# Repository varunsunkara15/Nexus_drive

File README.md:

# Nexus Drive

**Nexus Drive** is an open-hardware motor driver we are designing for a humanoid robot's joints.

The goal is a compact board that can sit near each joint actuator and drive its motor accurately and efficiently. It should also report back to the robot's main controller.

> **Status:** 🚧 Early development. Schematic in progress (power stage, gate driver, MCU, CAN-FD, encoders and sensing drawn; ERC has 0 errors; logic supplies, DC-link and input protection still to add); PCB layout not started.

---

## Repository layout

```
Nexus_drive/
├── hardware/                     KiCad 10 project (open nexus_drive.kicad_pro)
│   ├── nexus_drive.kicad_pro     Project file
│   ├── nexus_drive.kicad_sch     Root schematic sheet
│   ├── gate_driver.kicad_sch     DRV8353S gate driver and support parts
│   ├── h_bridge.kicad_sch        One half-bridge (MOSFETs, shunt, phase output), used 3× for phases A/B/C
│   ├── current_sense.kicad_sch   RC filters on the current-sense amplifier outputs
│   ├── stm32g474.kicad_sch       STM32G474METx MCU, wired to the pin plan
│   ├── can_fd.kicad_sch          TCAN1042GV CAN-FD transceiver and bus connectors
│   ├── encoders.kicad_sch        On-board MA702GQ encoder and external SPI encoder connectors
│   ├── sensing.kicad_sch         Bus and phase voltage dividers, FET and motor temperature inputs
│   ├── nexus_drive.kicad_sym     Project symbols (TCAN1042GV, MA702GQ, EMI filter)
│   ├── nexus_drive.kicad_pcb     PCB layout (not started)
│   ├── fp-lib-table, sym-lib-table   Project library tables
│   └── lib/                      Project-local symbol and footprint libraries (moteus)
├── firmware/
│   └── Comms Component Selection.ioc   STM32CubeMX pin assignment for the MCU
├── docs/
│   └── power-stage.md            Power stage design notes
├── LICENSES/, NOTICE.md          Attribution for files derived from mjbots moteus (Apache-2.0)
└── README.md
```

Folders for fabrication outputs (Gerbers, BOM, pick-and-place) and datasheets will be added as the design matures.

## Design goals

These are the intended targets. Values still marked **TBD** will be filled in as we choose parts. The power stage is described in detail in [docs/power-stage.md](docs/power-stage.md).

- **Motor type:** Brushless DC / PMSM motors used in humanoid joint actuators
- **Control:** Field-oriented control (FOC) for smooth, quiet torque control
- **Feedback:** Rotor position sensing (e.g. a magnetic encoder) and phase current sensing
- **Communication:** A bus to the robot's main controller, such as CAN / CAN-FD
- **Protection:** Over-current, over-voltage, under-voltage and over-temperature protection
- **Form factor:** Small enough to mount on or inside the joint actuator

### Planned specifications

| Parameter | Target |
| --- | --- |
| Battery | 12S3P Li-ion / LiPo: 36–50.4 V (44–48 V nominal) |
| Continuous / peak phase current | TBD (depends on the motor) |
| Microcontroller | STM32G474METx (LQFP-80, 170 MHz Cortex-M4) |
| Gate driver | TI DRV8353S (SPI-configured, integrated current-sense amplifiers) |
| MOSFETs | 6 × onsemi FDMT80080DC (80 V, 1.35 mΩ) |
| Current sensing | 3 low-side shunts (value TBD) |
| Overvoltage protection | Input TVS, bulk capacitor, 100 V ceramic DC-link bank, anti-spark connector |
| Encoder interface | 3 × SPI: on-board MA702GQ magnetic encoder, 2 external connectors |
| Communication | CAN-FD (TCAN1042GV), two daisy-chain connectors |
| Board dimensions | TBD |

### Note: bulk capacitance on the battery bus

The power stage in this repo has **no bulk / DC-link capacitor bank yet**. It is owned by another team member and must be added before the board is built. The reference design (moteus x1) uses 36 × 4.7 µF 100 V ceramics. A **bulk electrolytic (or tantalum) capacitor** at the power input may also be needed. Reasons:

- **Hot-plug ringing:** a bank of only ceramics has very low ESR. Together with the battery cable's inductance, it can ring up to ~2× the battery voltage when the battery is plugged in (~100 V on a 50.4 V pack), above the 80 V MOSFET rating. An electrolytic's higher ESR (≈ 0.05–0.1 Ω) damps this ringing.
- **Ceramics lose capacitance under DC bias:** 100 V X7R ceramics keep only about 30–50 % of their rated value at 50 V, so the real bus capacitance is much lower than the printed value.
- **Regen and load steps:** a larger capacitor absorbs some regenerative braking energy and supplies current during fast load changes, reducing bus voltage swings.

Guidance: rated **80 V or higher** (63 V is the bare minimum), capacitance several times the effective ceramic bank (e.g. 330–470 µF total), ESR ≈ 0.05–0.1 Ω, placed between the input connector and the half-bridges. **Tantalum is not recommended at this voltage:** tantalums need ~2× voltage derating (a >100 V part is hard to find), and they tend to fail short-circuit, which is a fire risk on a stiff 12S3P pack. Aluminium electrolytic or hybrid polymer is the safer choice. See [docs/power-stage.md](docs/power-stage.md) for the full overvoltage-protection requirements.

## Schematic review (27 Nov 2026)

This review covers the schematic at commit `345d5f4`. It was checked against the KiCad netlist, ERC, DRC with schematic parity, the pin plan in `firmware/STM32G474 Pinout.ioc`, and [hardware/comms-mcu-review.md](hardware/comms-mcu-review.md). Item numbers continue from the earlier reviews.

**Design intent: the board is deliberately over-specified.** The first target motors are the CubeMars **RO80 KV105** (≈15 A rated, ~50 A peak) and **RO100 KV55** (≈20 A rated, ~62 A peak) at 48 V. The power stage keeps moteus x1's 120 A-class parts so that larger motors can be used later.

**Checks:**
- **ERC:** 0 errors, plus 9 library-symbol warnings.
- **DRC:** 0 violations, 0 schematic-parity issues and 115 unrouted connections.
- **Pin plan:** the new pins in the `.ioc` match the schematic: status LED on PB6/PB7/PB9 and HC-05 STATE on PB11.

### ✅ Closed since 23 Nov
| Item | Resolution (verified against the netlist) |
|---|---|
| N3 | FL1 is ACT1210D-101-2P. TDK's drawing shows windings 1–4 and 2–3. The netlist runs U2 CANH → pin 1 → pin 4 → bus CANH, and CANL on 2 → 3. |
| N24 | **The earlier review was wrong.** The TI datasheet for the 40-pin package says the DVDD capacitor goes "between the DVDD and GND pins", and pin 39 is "Device power ground". C20 on `GNDPWR` (pin 39) is correct. The same table confirms C23 (VGLS → GND) and C19 + C38 (VM: 0.1 µF + ≥10 µF). |
| D7 | Part chosen: Nexperia PESD5V0S1BA. |
| N7 | The motor thermistor moved to J5 pins 13–14 (via R39 and D7). The firmware conversion is in `comms-mcu-review.md`. |
| N8 | J1 is a JST GH 5-pin, including the HC-05 STATE line to PB11. The cable mapping is documented. |
| N15 | The U6 pad geometry was checked against the MPS drawing. Confirm the stencil with the fab. |
| N17 | The SWD pinout is mapped to ST-LINK/V2 and STLINK-V3MINIE. The crystal (10 pF load) with 12 pF caps assumes about 4 pF of stray capacitance; check it on the first board. |
| N18 | Keep the 120 Ω and JP2. Close JP2 only at a bus end. |
| — | **New status LEDs:** D8 (3.3 V power) and D9 (RGB, MCU-driven). The firmware helper `NexusStatusLed_Update` writes the correct levels: low turns a colour on, high turns it off. |

### 🔴 Must add before the PCB can work
These are unchanged from 23 Nov, and routing has continued around them.
- [ ] **N20: no power input.** There's no connector or pads for `V+` and `GNDPWR`.
- [ ] **N21: no supply makes the logic rails.** `+12V` (DRV8353 VM), `+5V` (TCAN1042, HC-05) and `+3V`/`+3VA` have no source. See the 23 Nov power-tree table for a starting point: a buck from `V+` rated for ≥ 80 V input, then 5 V, then 3.3 V. Keep the board's idle draw under about 2 W so all 12 drivers fit the PDB precharge.
- [ ] **N22: DC-link capacitance is still only 3 × 0.1 µF.** Add the ceramic bank at the half-bridges and a bulk capacitor at the input, rated 80 V or more.
- [ ] **N23: no input TVS,** with 80 V MOSFETs on a 50.4 V bus. Regen must also be limited in firmware.
- [ ] **N4: stop routing near the power stage** until N20–N23 are in the schematic. Tracks routed there now are likely to move.

### 🟠 Should decide
- [ ] **N25: CAN now has a single 3-pin connector (J3).** Each driver hangs off the bus on a harness branch, and CAN-FD's fast data phase is sensitive to branch length. Either keep each branch to a few centimetres and agree the CAN-FD data rate with the harness owner, or, if the mechanics allow, use a 5-pin header with CANH/CANL in and out so the chain passes through the board.
- [ ] **N26: FL1 value.** The 100 µH ACT1210D-101 was chosen. TDK also makes a 51 µH version of the same choke. Check which one TDK specifies for your planned CAN-FD data rate.
- [ ] **N9, N10, N11, N13 are carried over:** current-sense gain per motor, gate-drive budget against PWM frequency, offset calibration, and thermal design for the over-spec rating. Plans are in `comms-mcu-review.md`, but they still need hardware confirmation.

### 🟡 Housekeeping
- [ ] **N27: voltage ratings missing from the values.** C23 (VGLS) needs **≥ 16 V** and C20 (DVDD) **≥ 6.3 V**. Add them to the values so the BOM is right.
- [ ] **N28: D9 green and blue may be dim and uneven** on the 3.3 V rail, because their forward voltage is close to 3 V. Check on the first board, and lower R42/R43 if needed.
- [ ] **N12 (rest):** a hard short on an encoder cable may still reset the MCU before F1/F2 trip. Confirm on hardware.
- [ ] **N19:** commit the literature review to `docs/`.
- [ ] The status line at the top of this README still says "PCB layout not started".

**Most important:** N20–N23. The board can't be powered until the input, logic supplies, DC-link capacitors and input protection are drawn.

## Getting started

### Requirements

- [KiCad](https://www.kicad.org/) **10.0** or newer. The project files use the KiCad 10 format and will not open in older versions.

### Opening the project

```bash
git clone https://github.com/varunsunkara15/Nexus_drive.git
cd Nexus_drive
```

Then open `hardware/nexus_drive.kicad_pro` in KiCad.

## Roadmap

- [x] Create the KiCad project and repository
- [ ] Define the specifications (battery voltage ✅, motor current, motor type)
- [ ] Choose the main parts (gate driver ✅, MOSFETs ✅, MCU ✅, shunts, encoder)
- [ ] Draw the schematic (phase power section ✅, gate driver ✅, MCU pin connections ✅, CAN-FD ✅, encoders ✅, sensing ✅, logic supplies, DC-link, input protection)
- [ ] Lay out the PCB
- [ ] Run design review, DRC and ERC
- [ ] Order and assemble the first prototype
- [ ] Bring up the board and write the firmware (FOC loop, communication)
- [ ] Test on a humanoid joint actuator

## Contributing

This project is under active development. Issues and pull requests are welcome. Please describe the change you're proposing, and why, before sending large design changes.

## License

No license has been chosen yet. Until one is added, all rights are reserved by the authors.

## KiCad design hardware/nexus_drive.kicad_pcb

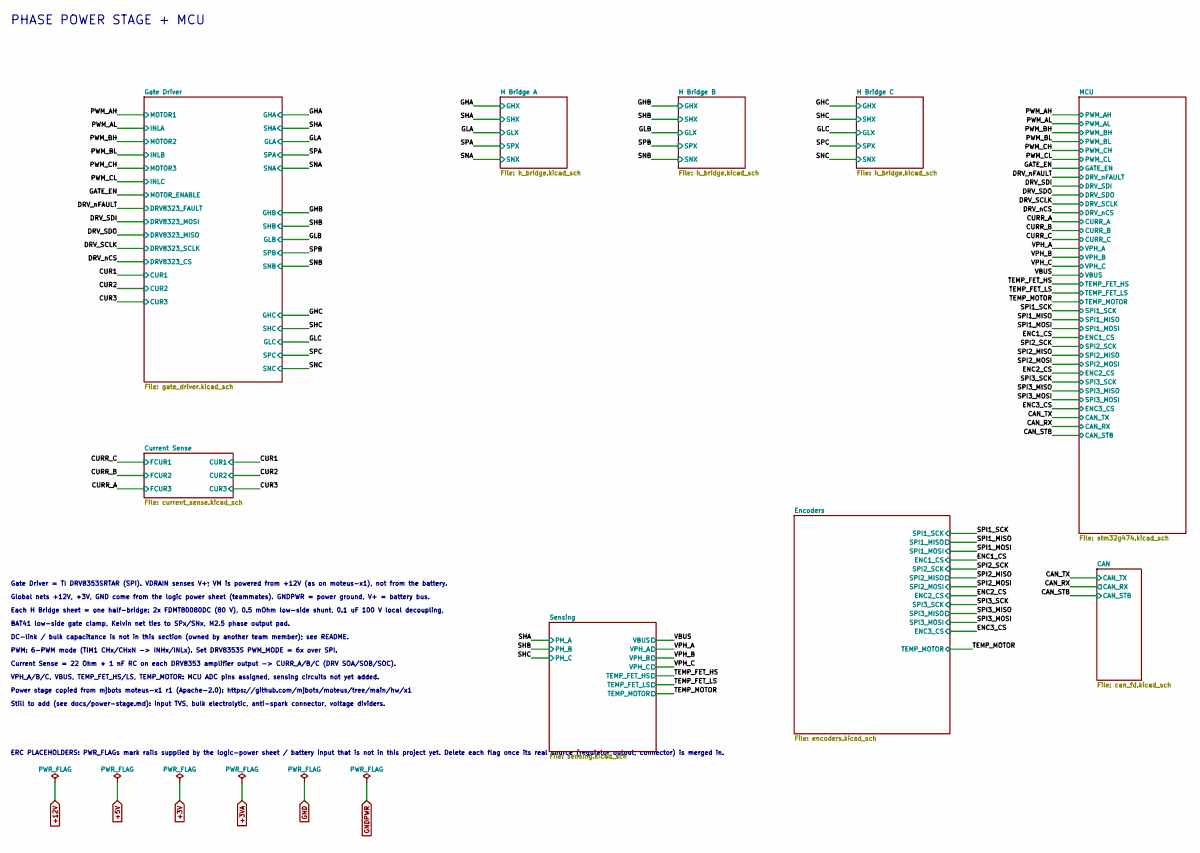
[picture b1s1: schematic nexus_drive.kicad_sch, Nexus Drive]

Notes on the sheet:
PWM: 6-PWM mode (TIM1 CHx/CHxN -> INHx/INLx). Set DRV8353S PWM_MODE = 6x over SPI.
Each H Bridge sheet = one half-bridge: 2x FDMT80080DC (80 V), 0.5 mOhm low-side shunt, 0.1 uF 100 V local decoupling,
Global nets +12V, +3V, GND come from the logic power sheet (teammates). GNDPWR = power ground, V+ = battery bus.
Gate Driver = TI DRV8353SRTAR (SPI). VDRAIN senses V+; VM is powered from +12V (as on moteus-x1), not from the battery.
DC-link / bulk capacitance is not in this section (owned by another team member); see README.
BAT41 low-side gate clamp, Kelvin net ties to SPx/SNx, M2.5 phase output pad.
Power stage copied from mjbots moteus-x1 r1 (Apache-2.0): https://github.com/mjbots/moteus/tree/main/hw/x1
Current Sense = 22 Ohm + 1 nF RC on each DRV8353 amplifier output -> CURR_A/B/C (DRV SOA/SOB/SOC).
ERC PLACEHOLDERS: PWR_FLAGs mark rails supplied by the logic-power sheet / battery input that is not in this project yet. Delete each flag once its real source (regulator output, connector) is merged in.
PHASE POWER STAGE + MCU
VPH_A/B/C, VBUS, TEMP_FET_HS/LS, TEMP_MOTOR: MCU ADC pins assigned, sensing circuits not yet added.
Still to add (see docs/power-stage.md): input TVS, bulk electrolytic, anti-spark connector, voltage dividers.

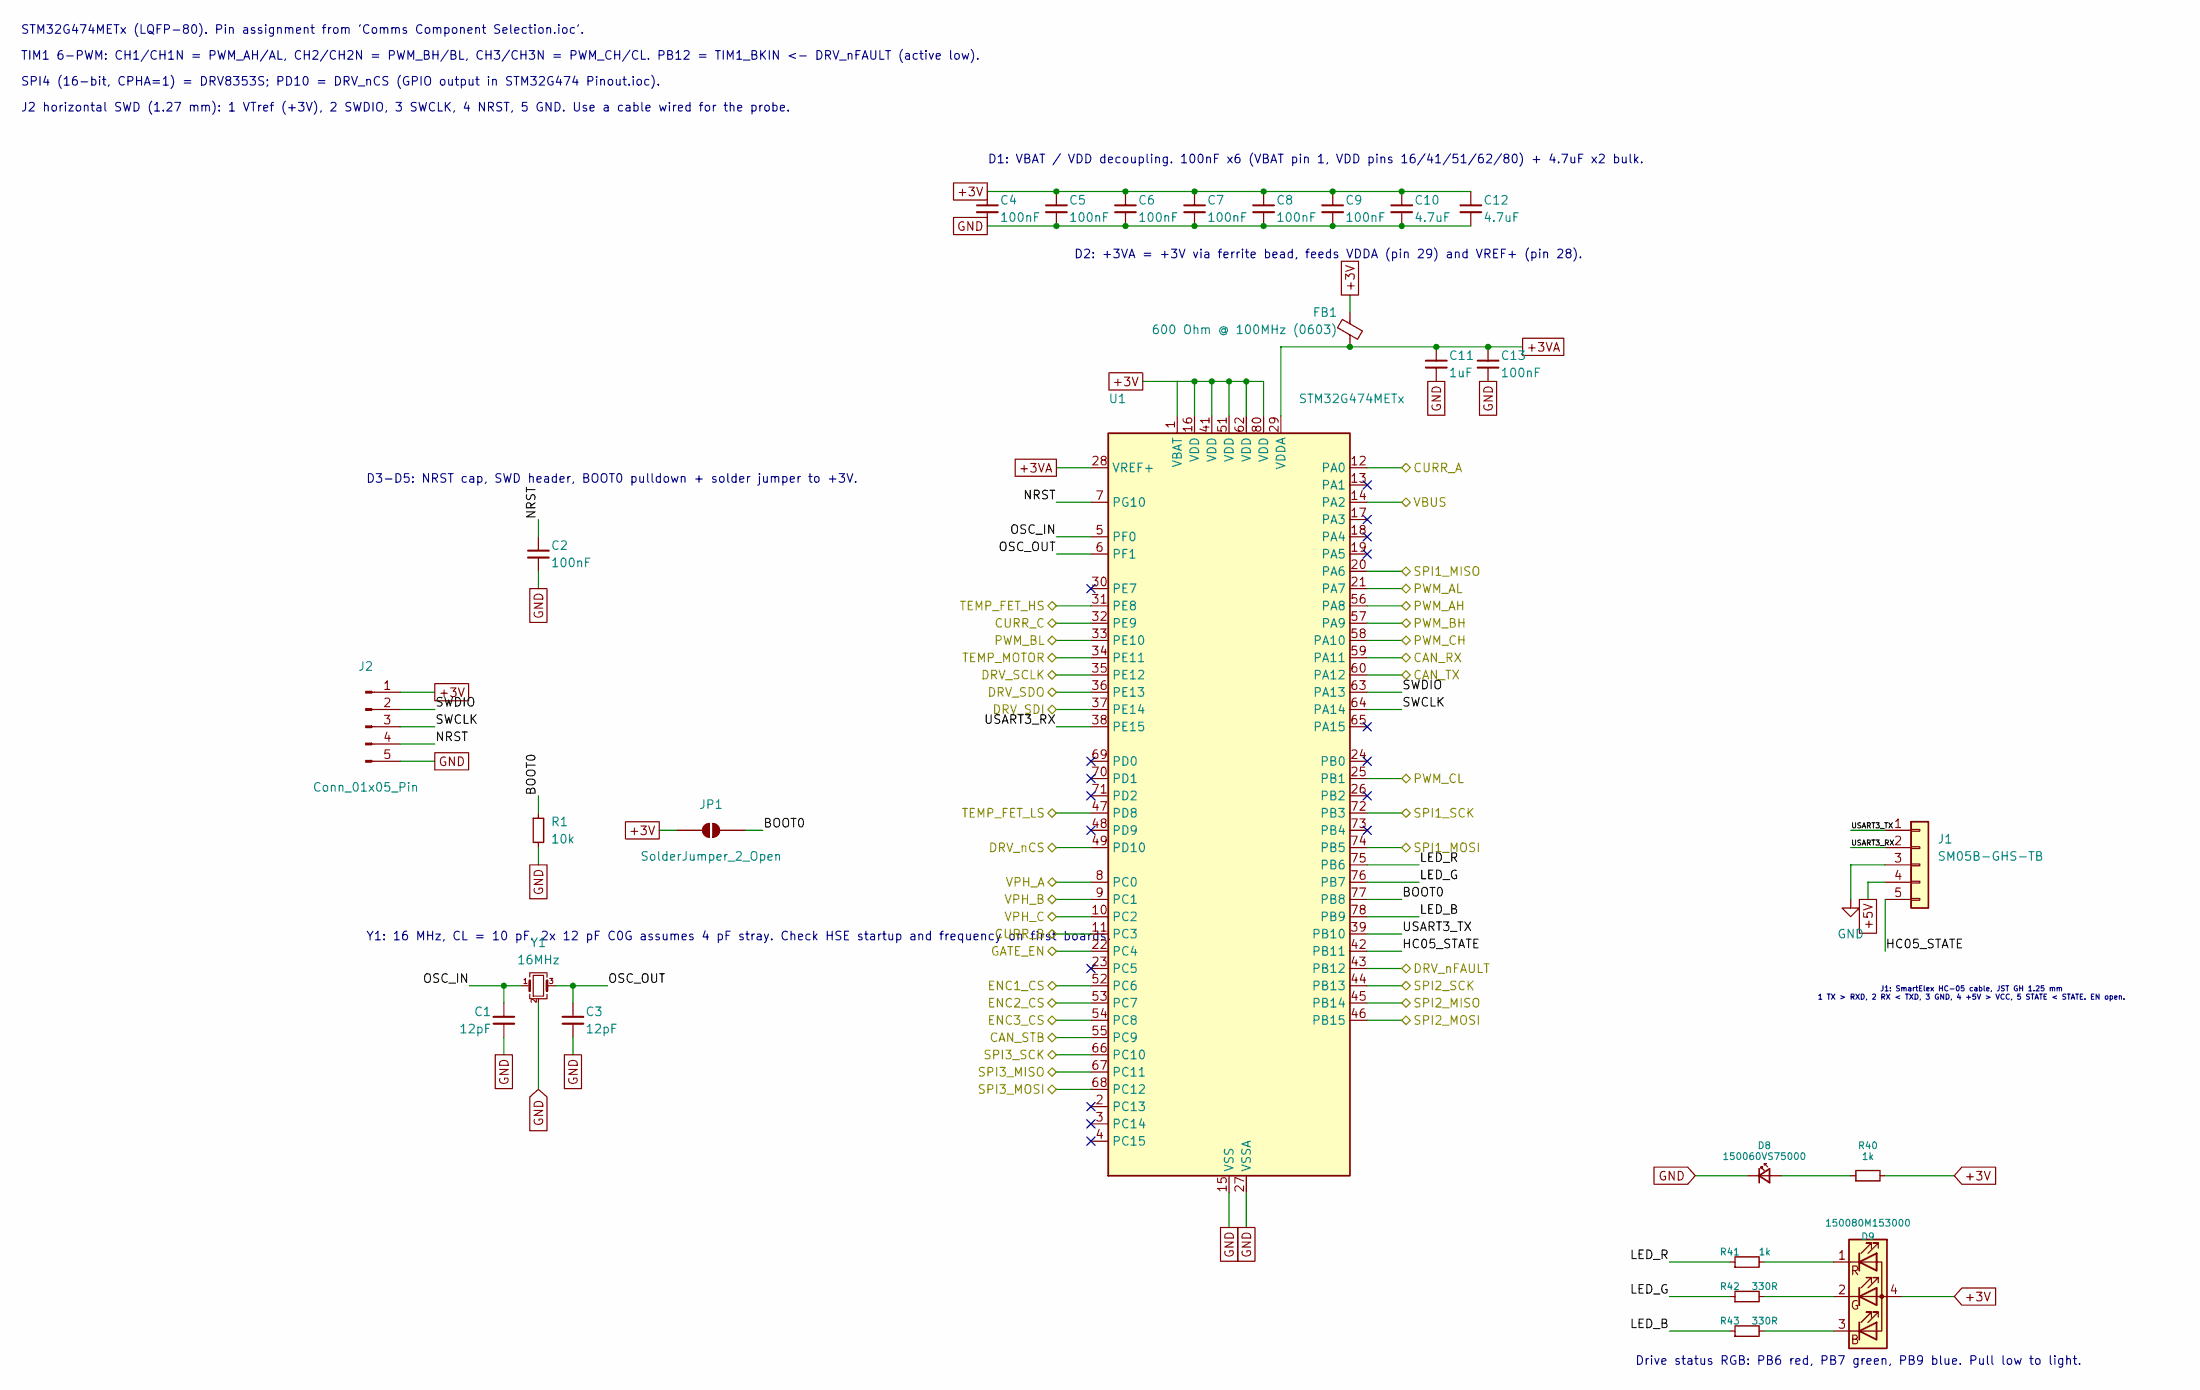
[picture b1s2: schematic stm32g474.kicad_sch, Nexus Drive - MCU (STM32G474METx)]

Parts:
C1, C3: 12pF; C_0603_1608Metric
C2, C4, C5, C6, C7, C8, C9, C13: 100nF; C_0603_1608Metric
C10, C12: 4.7uF; C_0805_2012Metric
C11: 1uF; C_0603_1608Metric
D8: 150060VS75000; LED_0603_1608Metric
D9: 150080M153000; LED_RGB_Wuerth_150080M153000
FB1: 600 Ohm @ 100MHz (0603); L_0603_1608Metric
J1: SM05B-GHS-TB; JST_GH_SM05B-GHS-TB_1x05-1MP_P1.25mm_Horizontal
J2: Conn_01x05_Pin; PinHeader_1x05_P1.27mm_Horizontal
JP1: SolderJumper_2_Open; SolderJumper-2_P1.3mm_Open_Pad1.0x1.5mm
R1: 10k; R_0603_1608Metric
R40, R41: 1k; R_0603_1608Metric
R42, R43: 330R; R_0603_1608Metric
U1: STM32G474METx; LQFP-80_12x12mm_P0.5mm
Y1: 16MHz; Crystal_SMD_3225-4Pin_3.2x2.5mm; MPN ABM8-16.000MHZ-10-1-U-T

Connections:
+3V: C4.1, C5.1, C6.1, C7.1, C8.1, C9.1, C10.1, C12.1, D9.4 (A), FB1.1, J2.1, JP1.1 (A), R40.2, U1.1 (VBAT), U1.16 (VDD), U1.41 (VDD), U1.51 (VDD), U1.62 (VDD), U1.80 (VDD); also elsewhere on the board
+3VA: C11.1, C13.1, FB1.2, U1.28 (VREF+), U1.29 (VDDA); also elsewhere on the board
+5V: J1.4; also elsewhere on the board
/CAN_RX: U1.59 (PA11); also elsewhere on the board
/CAN_STB: U1.55 (PC9); also elsewhere on the board
/CAN_TX: U1.60 (PA12); also elsewhere on the board
/CURR_A: U1.12 (PA0); also elsewhere on the board
/CURR_B: U1.11 (PC3); also elsewhere on the board
/CURR_C: U1.32 (PE9); also elsewhere on the board
/DRV_SCLK: U1.35 (PE12); also elsewhere on the board
/DRV_SDI: U1.37 (PE14); also elsewhere on the board
/DRV_SDO: U1.36 (PE13); also elsewhere on the board
/DRV_nCS: U1.49 (PD10); also elsewhere on the board
/DRV_nFAULT: U1.43 (PB12); also elsewhere on the board
/ENC1_CS: U1.52 (PC6); also elsewhere on the board
/ENC2_CS: U1.53 (PC7); also elsewhere on the board
/ENC3_CS: U1.54 (PC8); also elsewhere on the board
/GATE_EN: U1.22 (PC4); also elsewhere on the board
/MCU/BOOT0: JP1.2 (B), R1.1, U1.77 (PB8)
/MCU/HC05_STATE: J1.5, U1.42 (PB11)
/MCU/LED_B: R43.1, U1.78 (PB9)
/MCU/LED_G: R42.1, U1.76 (PB7)
/MCU/LED_R: R41.1, U1.75 (PB6)
/MCU/NRST: C2.1, J2.4, U1.7 (PG10)
/MCU/OSC_IN: C1.1, U1.5 (PF0), Y1.1
/MCU/OSC_OUT: C3.1, U1.6 (PF1), Y1.3
/MCU/SWCLK: J2.3, U1.64 (PA14)
/MCU/SWDIO: J2.2, U1.63 (PA13)
/MCU/USART3_RX: J1.2, U1.38 (PE15)
/MCU/USART3_TX: J1.1, U1.39 (PB10)
/PWM_AH: U1.56 (PA8); also elsewhere on the board
/PWM_AL: U1.21 (PA7); also elsewhere on the board
/PWM_BH: U1.57 (PA9); also elsewhere on the board
/PWM_BL: U1.33 (PE10); also elsewhere on the board
/PWM_CH: U1.58 (PA10); also elsewhere on the board
/PWM_CL: U1.25 (PB1); also elsewhere on the board
/SPI1_MISO: U1.20 (PA6); also elsewhere on the board
/SPI1_MOSI: U1.74 (PB5); also elsewhere on the board
/SPI1_SCK: U1.72 (PB3); also elsewhere on the board
/SPI2_MISO: U1.45 (PB14); also elsewhere on the board
/SPI2_MOSI: U1.46 (PB15); also elsewhere on the board
/SPI2_SCK: U1.44 (PB13); also elsewhere on the board
/SPI3_MISO: U1.67 (PC11); also elsewhere on the board
/SPI3_MOSI: U1.68 (PC12); also elsewhere on the board
/SPI3_SCK: U1.66 (PC10); also elsewhere on the board
/TEMP_FET_HS: U1.31 (PE8); also elsewhere on the board
/TEMP_FET_LS: U1.47 (PD8); also elsewhere on the board
/TEMP_MOTOR: U1.34 (PE11); also elsewhere on the board
/VBUS: U1.14 (PA2); also elsewhere on the board
/VPH_A: U1.8 (PC0); also elsewhere on the board
/VPH_B: U1.9 (PC1); also elsewhere on the board
/VPH_C: U1.10 (PC2); also elsewhere on the board
GND: C1.2, C2.2, C3.2, C4.2, C5.2, C6.2, C7.2, C8.2, C9.2, C10.2, C11.2, C12.2, C13.2, D8.1 (K), J1.3, J2.5, R1.2, U1.15 (VSS), U1.27 (VSSA), U1.40 (VSS), U1.50 (VSS), U1.61 (VSS), U1.79 (VSS), Y1.2 (G), Y1.4 (G); also elsewhere on the board
unnamed: D8.2 (A), R40.1
unnamed: D9.3 (BK), R43.2
unnamed: D9.2 (GK), R42.2
unnamed: D9.1 (RK), R41.2

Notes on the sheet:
D2: +3VA = +3V via ferrite bead, feeds VDDA (pin 29) and VREF+ (pin 28).
J1: SmartElex HC-05 cable, JST GH 1.25 mm 1 TX > RXD, 2 RX < TXD, 3 GND, 4 +5V > VCC, 5 STATE < STATE. EN open.
J2 horizontal SWD (1.27 mm): 1 VTref (+3V), 2 SWDIO, 3 SWCLK, 4 NRST, 5 GND. Use a cable wired for the probe.
SPI4 (16-bit, CPHA=1) = DRV8353S; PD10 = DRV_nCS (GPIO output in STM32G474 Pinout.ioc).
D1: VBAT / VDD decoupling. 100nF x6 (VBAT pin 1, VDD pins 16/41/51/62/80) + 4.7uF x2 bulk.
Y1: 16 MHz, CL = 10 pF. 2x 12 pF C0G assumes 4 pF stray. Check HSE startup and frequency on first boards.
STM32G474METx (LQFP-80). Pin assignment from 'Comms Component Selection.ioc'.
TIM1 6-PWM: CH1/CH1N = PWM_AH/AL, CH2/CH2N = PWM_BH/BL, CH3/CH3N = PWM_CH/CL. PB12 = TIM1_BKIN <- DRV_nFAULT (active low).
D3-D5: NRST cap, SWD header, BOOT0 pulldown + solder jumper to +3V.
Drive status RGB: PB6 red, PB7 green, PB9 blue. Pull low to light.

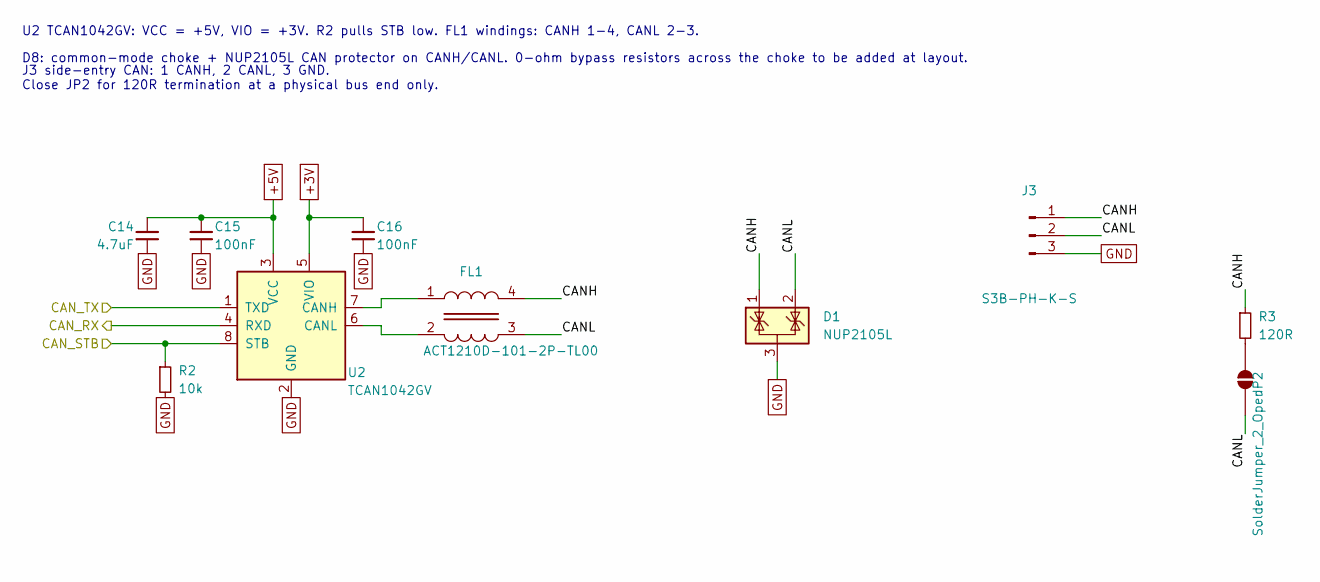
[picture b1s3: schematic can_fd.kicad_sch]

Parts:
C14: 4.7uF; C_0805_2012Metric
C15, C16: 100nF; C_0603_1608Metric
D1: NUP2105L; SOT-23
FL1: ACT1210D-101-2P-TL00; L_CommonMode_TDK_ACT1210D
J3: S3B-PH-K-S; JST_PH_S3B-PH-K_1x03_P2.00mm_Horizontal
JP2: SolderJumper_2_Open; SolderJumper-2_P1.3mm_Open_Pad1.0x1.5mm
R2: 10k; R_0603_1608Metric
R3: 120R; R_0603_1608Metric
U2: TCAN1042GV; SOIC-8_3.9x4.9mm_P1.27mm

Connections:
+3V: C16.1, U2.5 (VIO); also elsewhere on the board
+5V: C14.1, C15.1, U2.3 (VCC); also elsewhere on the board
/CAN/CANH: D1.1 (K), FL1.4, J3.1, R3.1
/CAN/CANL: D1.2 (K), FL1.3, J3.2, JP2.2 (B)
/CAN_RX: U2.4 (RXD); also elsewhere on the board
/CAN_STB: R2.1, U2.8 (STB); also elsewhere on the board
/CAN_TX: U2.1 (TXD); also elsewhere on the board
GND: C14.2, C15.2, C16.2, D1.3 (A), J3.3, R2.2, U2.2 (GND); also elsewhere on the board
unnamed: JP2.1 (A), R3.2
unnamed: FL1.1, U2.7 (CANH)
unnamed: FL1.2, U2.6 (CANL)

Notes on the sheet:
D8: common-mode choke + NUP2105L CAN protector on CANH/CANL. 0-ohm bypass resistors across the choke to be added at layout.
U2 TCAN1042GV: VCC = +5V, VIO = +3V. R2 pulls STB low. FL1 windings: CANH 1-4, CANL 2-3.
J3 side-entry CAN: 1 CANH, 2 CANL, 3 GND. Close JP2 for 120R termination at a physical bus end only.

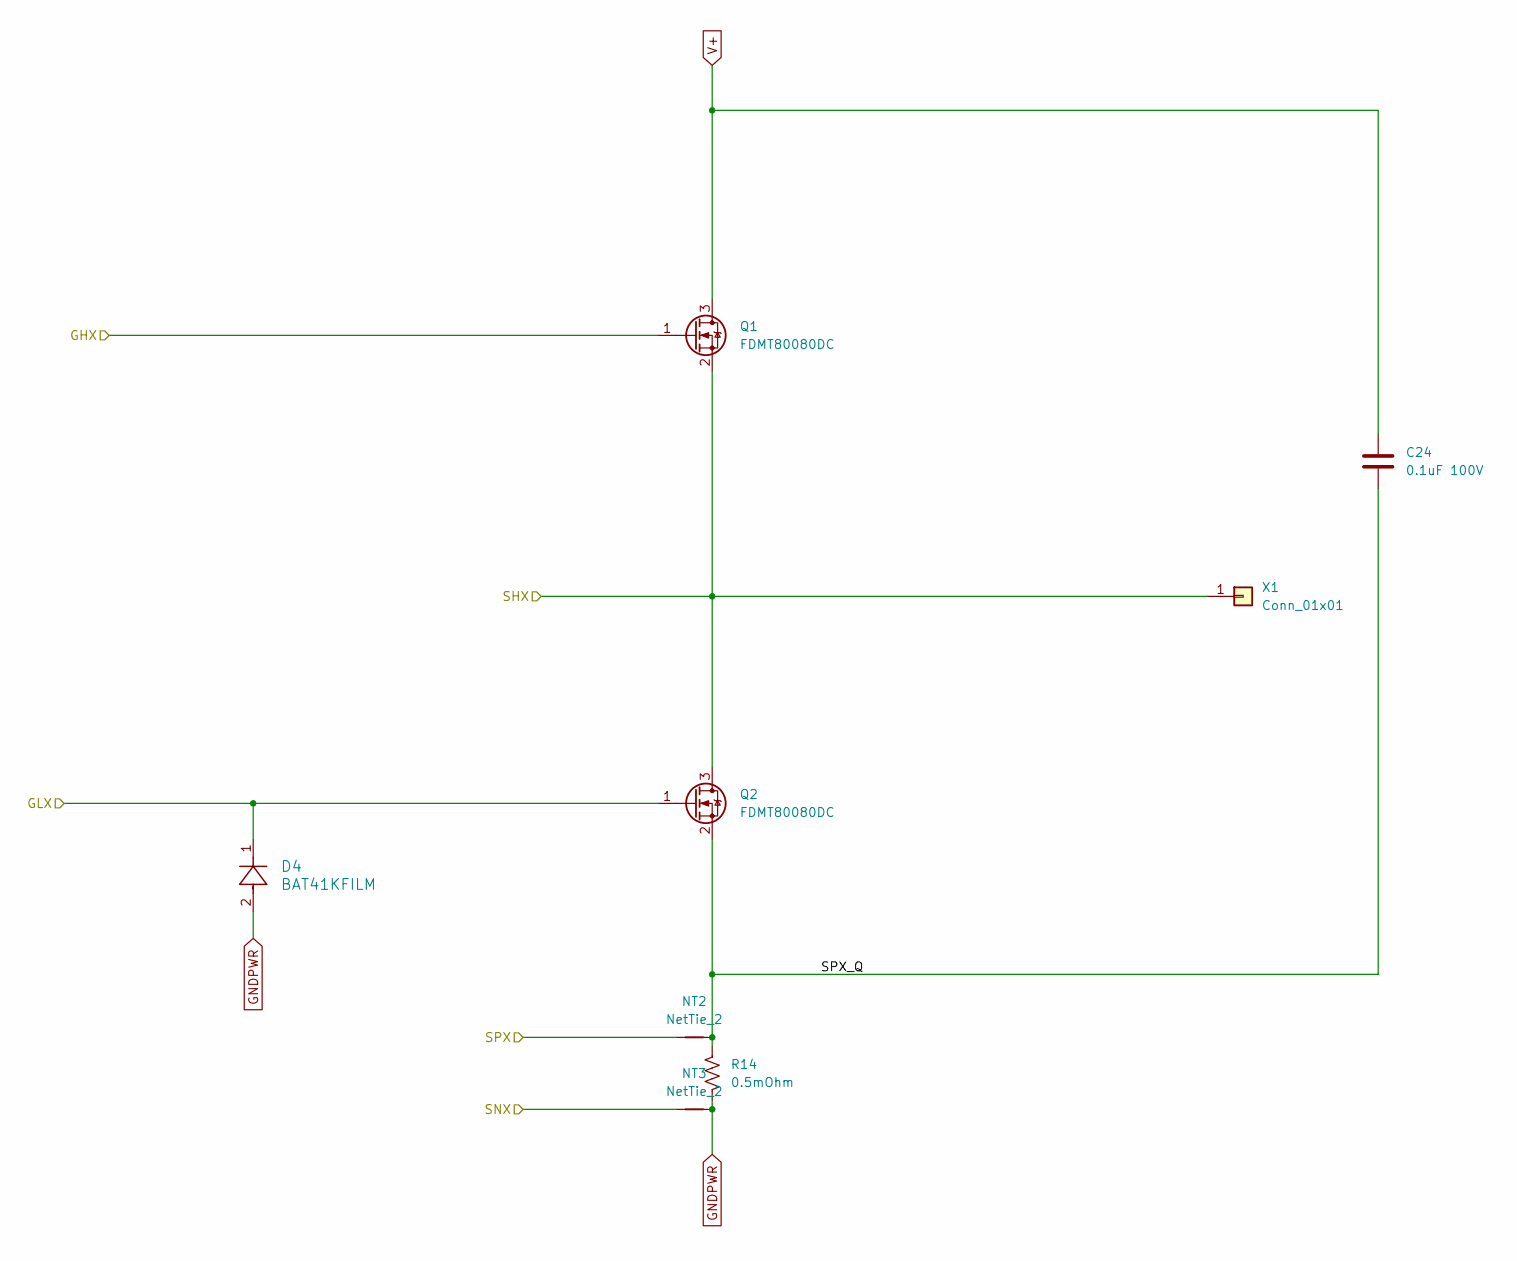
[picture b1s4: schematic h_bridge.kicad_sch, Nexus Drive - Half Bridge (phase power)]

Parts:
C24: 0.1uF 100V; C_1812_4532Metric; MPN 18121C104MAT2A
D4: BAT41KFILM; SOD-523_STM; MPN BAT41KFILM
NT2, NT3: NetTie_2; NetTie-2_SMD_Pad0.2
Q1, Q2: FDMT80080DC; PQFN_8x8; MPN FDMT80080DC
R14: 0.5mOhm; R_2512_6332Metric; MPN WSLF2512L5000FEA
X1: Conn_01x01; PhasePad_1.91mm

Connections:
/GHA: Q1.1 (G); also elsewhere on the board
/GLA: D4.1, Q2.1 (G); also elsewhere on the board
/H Bridge A/SPX_Q: C24.2, NT2.2, Q2.2 (S), R14.1
/SHA: Q1.2 (S), Q2.3 (D), X1.1 (Pin_1_1); also elsewhere on the board
/SNA: NT3.1; also elsewhere on the board
/SPA: NT2.1; also elsewhere on the board
GNDPWR: D4.2, NT3.2, R14.2; also elsewhere on the board
V+: C24.1, Q1.3 (D); also elsewhere on the board

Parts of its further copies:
C25, C26: 0.1uF 100V; C_1812_4532Metric; MPN 18121C104MAT2A
D5, D6: BAT41KFILM; SOD-523_STM; MPN BAT41KFILM
NT4, NT5, NT6, NT7: NetTie_2; NetTie-2_SMD_Pad0.2
Q3, Q4, Q5, Q6: FDMT80080DC; PQFN_8x8; MPN FDMT80080DC
R15, R16: 0.5mOhm; R_2512_6332Metric; MPN WSLF2512L5000FEA
X2, X3: Conn_01x01; PhasePad_1.91mm

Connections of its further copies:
/GHB: Q3.1 (G); also elsewhere on the board
/GHC: Q5.1 (G); also elsewhere on the board
/GLB: D5.1, Q4.1 (G); also elsewhere on the board
/GLC: D6.1, Q6.1 (G); also elsewhere on the board
/H Bridge B/SPX_Q: C25.2, NT4.2, Q4.2 (S), R15.1
/H Bridge C/SPX_Q: C26.2, NT6.2, Q6.2 (S), R16.1
/SHB: Q3.2 (S), Q4.3 (D), X2.1 (Pin_1_1); also elsewhere on the board
/SHC: Q5.2 (S), Q6.3 (D), X3.1 (Pin_1_1); also elsewhere on the board
/SNB: NT5.1; also elsewhere on the board
/SNC: NT7.1; also elsewhere on the board
/SPB: NT4.1; also elsewhere on the board
/SPC: NT6.1; also elsewhere on the board
GNDPWR: D5.2, D6.2, NT5.2, NT7.2, R15.2, R16.2; also elsewhere on the board
V+: C25.1, C26.1, Q3.3 (D), Q5.3 (D); also elsewhere on the board

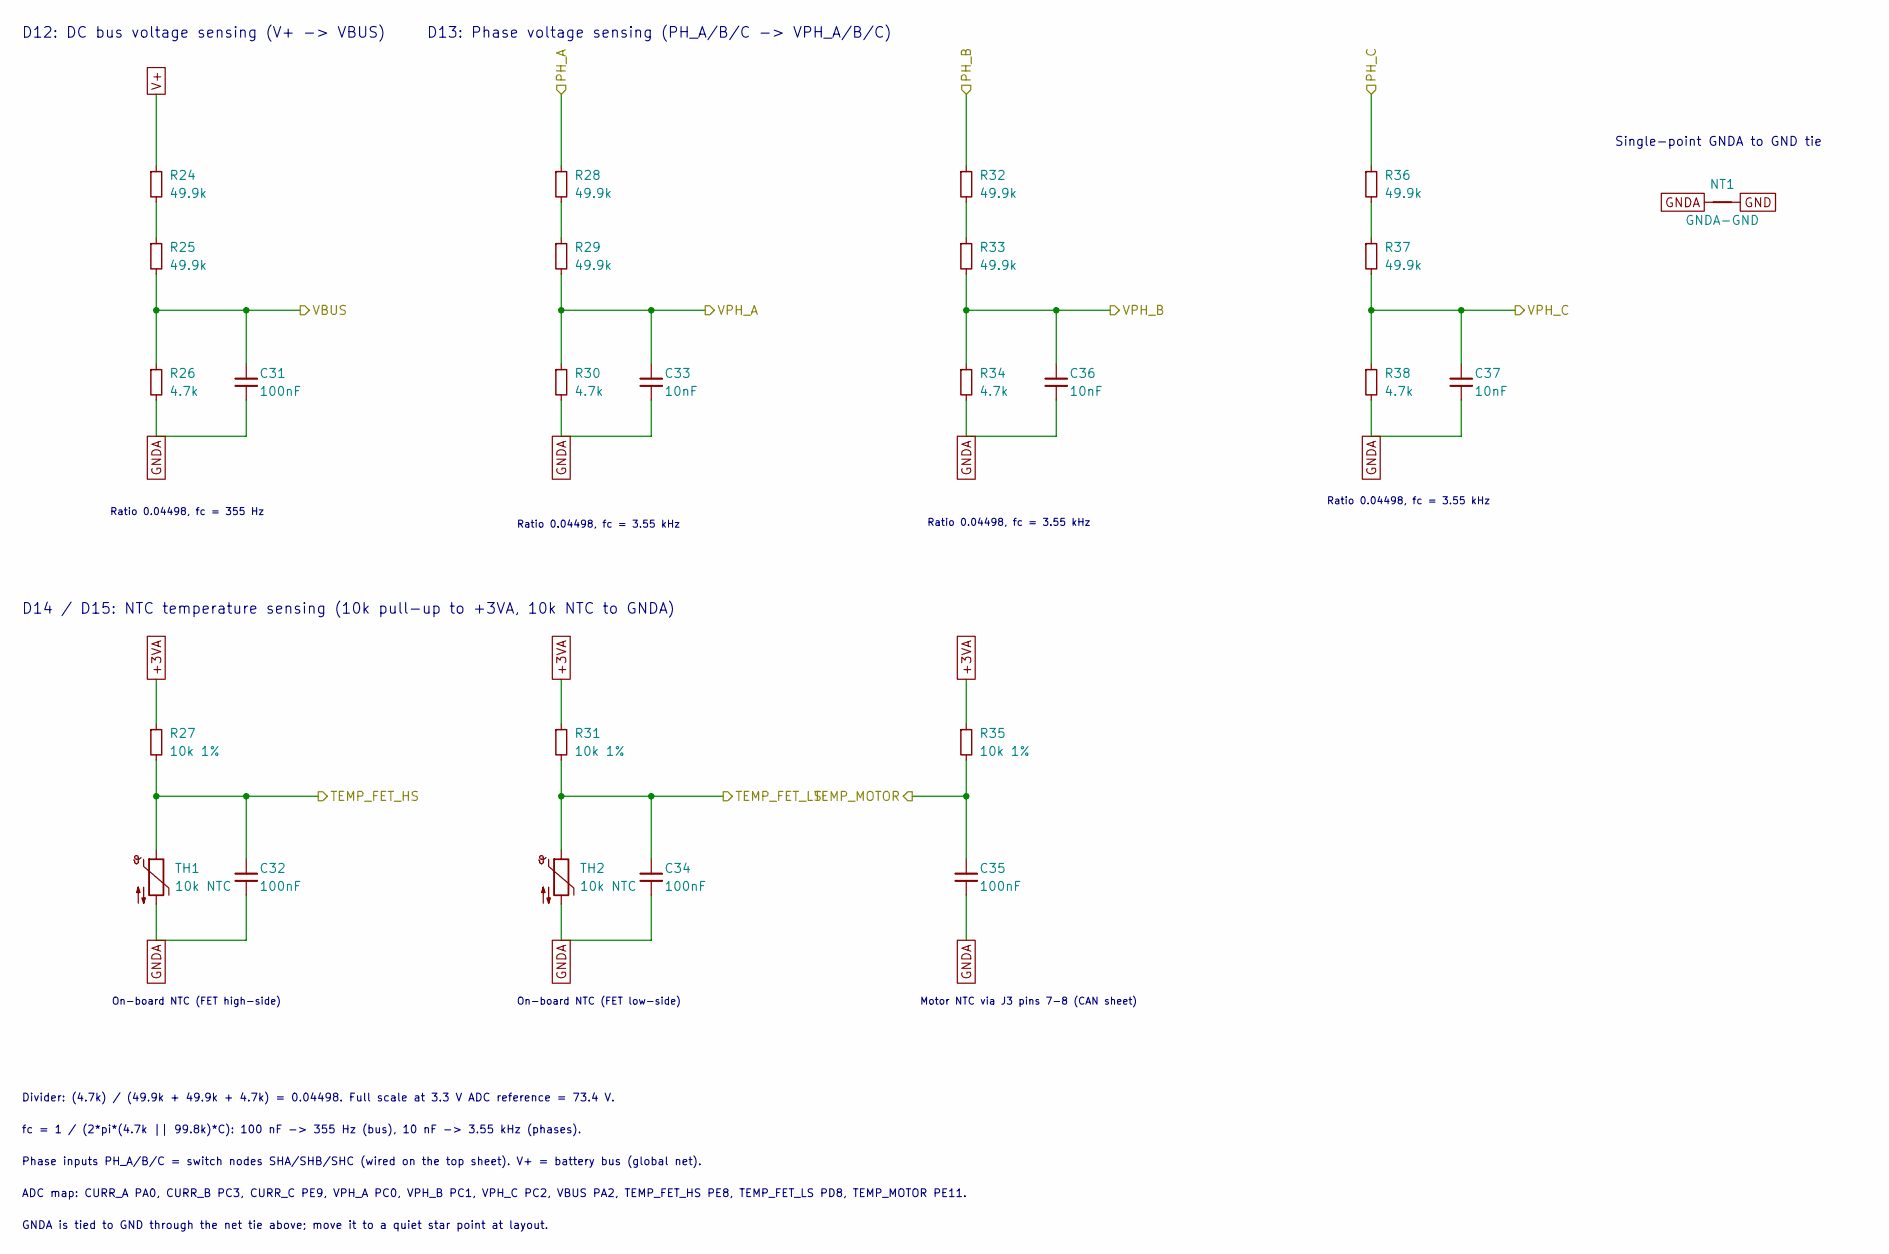
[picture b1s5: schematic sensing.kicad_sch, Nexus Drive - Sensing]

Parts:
C31, C32, C34, C35: 100nF; C_0603_1608Metric
C33, C36, C37: 10nF; C_0603_1608Metric
NT1: GNDA-GND; NetTie-2_SMD_Pad0.5mm
R24, R25, R28, R29, R32, R33, R36, R37: 49.9k; R_0805_2012Metric
R26, R30, R34, R38: 4.7k; R_0603_1608Metric
R27, R31, R35: 10k 1%; R_0603_1608Metric
TH1, TH2: 10k NTC; R_0603_1608Metric

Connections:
+3VA: R27.1, R31.1, R35.1; also elsewhere on the board
/SHA: R28.1; also elsewhere on the board
/SHB: R32.1; also elsewhere on the board
/SHC: R36.1; also elsewhere on the board
/TEMP_FET_HS: C32.1, R27.2, TH1.1; also elsewhere on the board
/TEMP_FET_LS: C34.1, R31.2, TH2.1; also elsewhere on the board
/TEMP_MOTOR: C35.1, R35.2; also elsewhere on the board
/VBUS: C31.1, R25.2, R26.1; also elsewhere on the board
/VPH_A: C33.1, R29.2, R30.1; also elsewhere on the board
/VPH_B: C36.1, R33.2, R34.1; also elsewhere on the board
/VPH_C: C37.1, R37.2, R38.1; also elsewhere on the board
GND: NT1.2; also elsewhere on the board
GNDA: C31.2, C32.2, C33.2, C34.2, C35.2, C36.2, C37.2, NT1.1, R26.2, R30.2, R34.2, R38.2, TH1.2, TH2.2; also elsewhere on the board
unnamed: R24.2, R25.1
unnamed: R28.2, R29.1
unnamed: R32.2, R33.1
unnamed: R36.2, R37.1
V+: R24.1; also elsewhere on the board

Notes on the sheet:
Phase inputs PH_A/B/C = switch nodes SHA/SHB/SHC (wired on the top sheet). V+ = battery bus (global net).
Ratio 0.04498, fc = 355 Hz
Motor NTC via J3 pins 7-8 (CAN sheet)
D14 / D15: NTC temperature sensing (10k pull-up to +3VA, 10k NTC to GNDA)
On-board NTC (FET high-side)
Ratio 0.04498, fc = 3.55 kHz
GNDA is tied to GND through the net tie above; move it to a quiet star point at layout.
Single-point GNDA to GND tie
D12: DC bus voltage sensing (V+ -> VBUS)
D13: Phase voltage sensing (PH_A/B/C -> VPH_A/B/C)
ADC map: CURR_A PA0, CURR_B PC3, CURR_C PE9, VPH_A PC0, VPH_B PC1, VPH_C PC2, VBUS PA2, TEMP_FET_HS PE8, TEMP_FET_LS PD8, TEMP_MOTOR PE11.
Divider: (4.7k) / (49.9k + 49.9k + 4.7k) = 0.04498. Full scale at 3.3 V ADC reference = 73.4 V.
On-board NTC (FET low-side)
fc = 1 / (2*pi*(4.7k || 99.8k)*C): 100 nF -> 355 Hz (bus), 10 nF -> 3.55 kHz (phases).

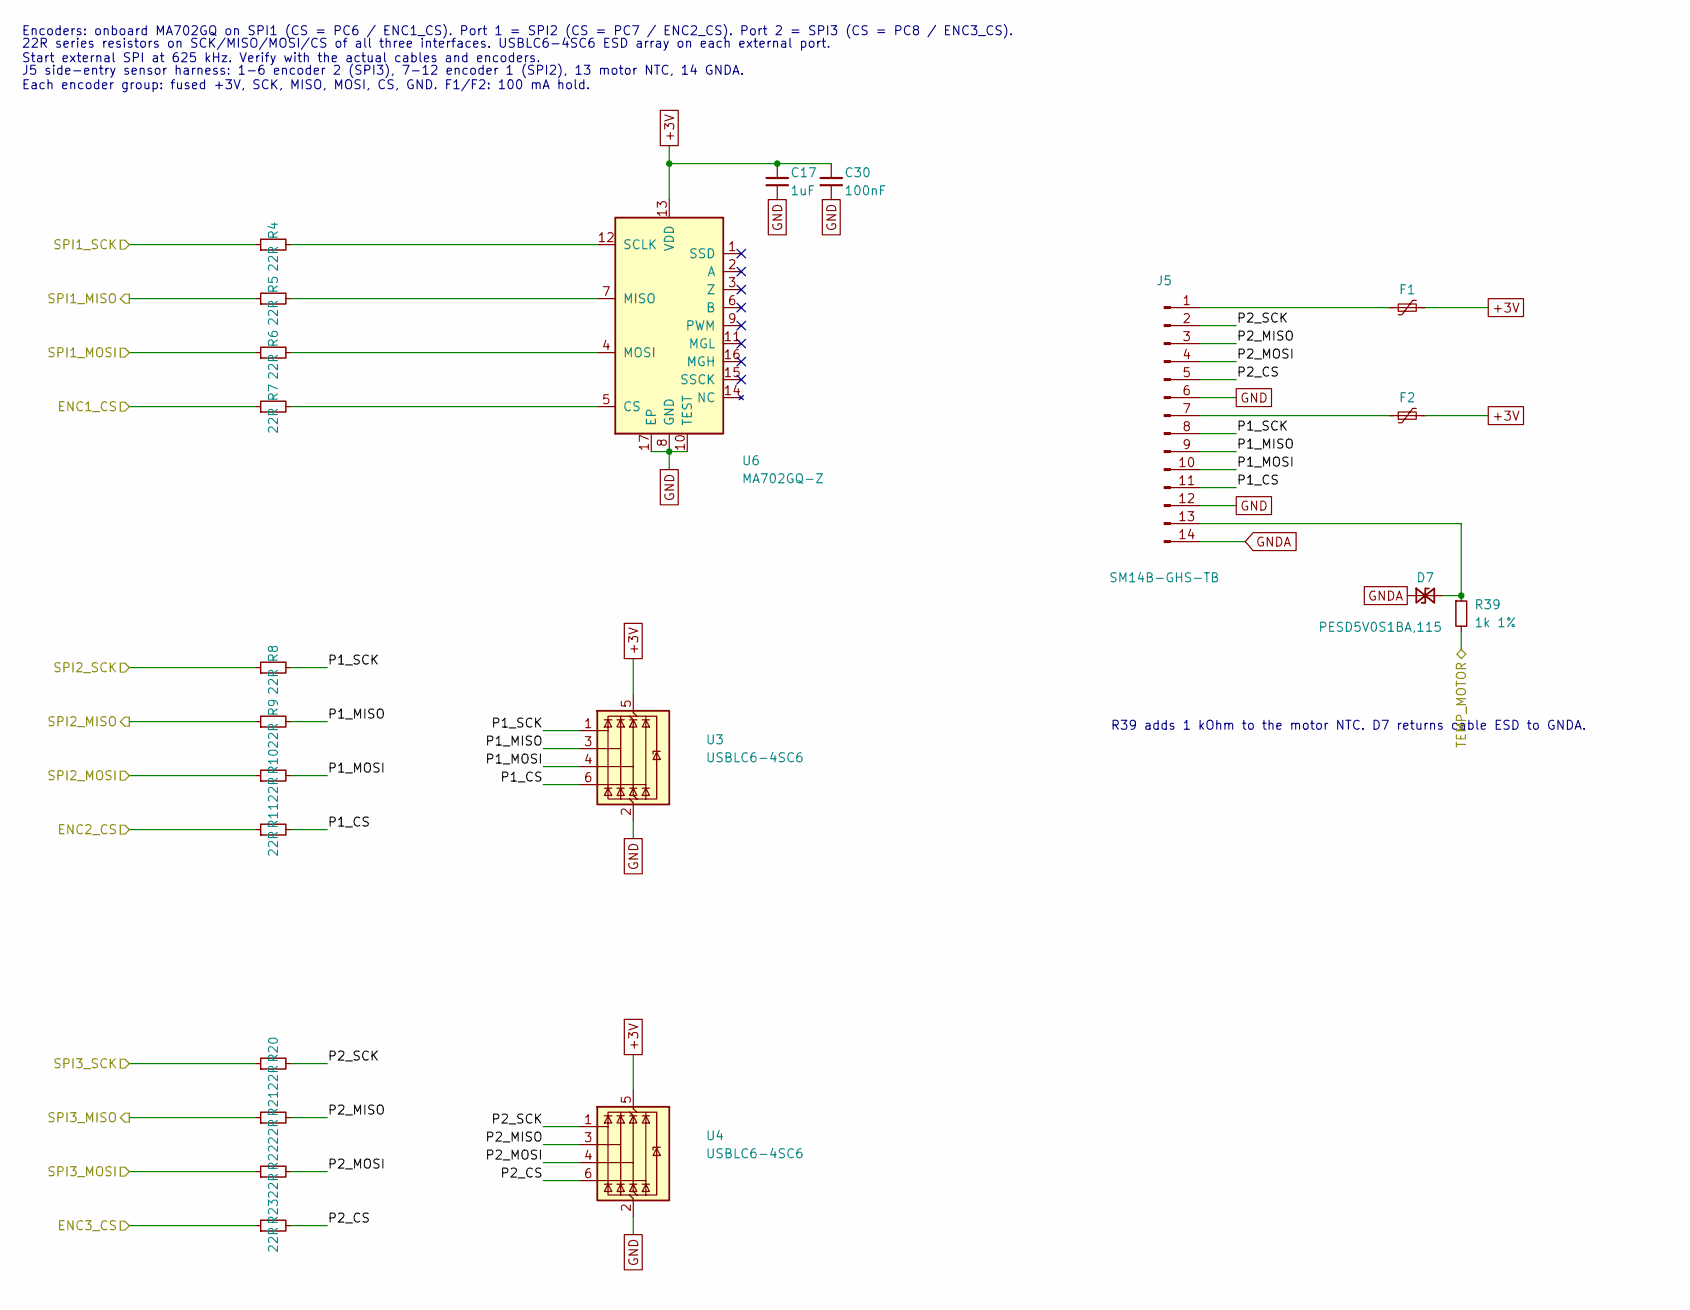
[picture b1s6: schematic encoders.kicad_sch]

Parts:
C17: 1uF; C_0603_1608Metric
C30: 100nF; C_0603_1608Metric
D7: PESD5V0S1BA,115; D_SOD-323
F1, F2: PTC 100mA hold; Fuse_0805_2012Metric
J5: SM14B-GHS-TB; JST_GH_SM14B-GHS-TB_1x14-1MP_P1.25mm_Horizontal
R4, R5, R6, R7, R8, R9, R10, R11, R20, R21, R22, R23: 22R; R_0603_1608Metric
R39: 1k 1%; R_0603_1608Metric
U3, U4: USBLC6-4SC6; SOT-23-6
U6: MA702GQ-Z; QFN-16-1EP_3x3mm_P0.5mm_EP1.7x1.7mm

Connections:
+3V: C17.1, C30.1, F1.2, F2.2, U3.5 (VBUS), U4.5 (VBUS), U6.13 (VDD); also elsewhere on the board
/ENC1_CS: R7.1; also elsewhere on the board
/ENC2_CS: R11.1; also elsewhere on the board
/ENC3_CS: R23.1; also elsewhere on the board
/Encoders/P1_CS: J5.11, R11.2, U3.6 (I/O4)
/Encoders/P1_MISO: J5.9, R9.2, U3.3 (I/O2)
/Encoders/P1_MOSI: J5.10, R10.2, U3.4 (I/O3)
/Encoders/P1_SCK: J5.8, R8.2, U3.1 (I/O1)
/Encoders/P2_CS: J5.5, R23.2, U4.6 (I/O4)
/Encoders/P2_MISO: J5.3, R21.2, U4.3 (I/O2)
/Encoders/P2_MOSI: J5.4, R22.2, U4.4 (I/O3)
/Encoders/P2_SCK: J5.2, R20.2, U4.1 (I/O1)
/SPI1_MISO: R5.1; also elsewhere on the board
/SPI1_MOSI: R6.1; also elsewhere on the board
/SPI1_SCK: R4.1; also elsewhere on the board
/SPI2_MISO: R9.1; also elsewhere on the board
/SPI2_MOSI: R10.1; also elsewhere on the board
/SPI2_SCK: R8.1; also elsewhere on the board
/SPI3_MISO: R21.1; also elsewhere on the board
/SPI3_MOSI: R22.1; also elsewhere on the board
/SPI3_SCK: R20.1; also elsewhere on the board
/TEMP_MOTOR: R39.2; also elsewhere on the board
GND: C17.2, C30.2, J5.6, J5.12, U3.2 (GND), U4.2 (GND), U6.8 (GND), U6.10 (TEST), U6.17 (EP); also elsewhere on the board
GNDA: D7.1 (A1), J5.14; also elsewhere on the board
unnamed: D7.2 (A2), J5.13, R39.1
unnamed: F1.1, J5.1
unnamed: F2.1, J5.7
unnamed: R7.2, U6.5 (CS)
unnamed: R5.2, U6.7 (MISO)
unnamed: R6.2, U6.4 (MOSI)
unnamed: R4.2, U6.12 (SCLK)

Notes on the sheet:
J5 side-entry sensor harness: 1-6 encoder 2 (SPI3), 7-12 encoder 1 (SPI2), 13 motor NTC, 14 GNDA. Each encoder group: fused +3V, SCK, MISO, MOSI, CS, GND. F1/F2: 100 mA hold.
22R series resistors on SCK/MISO/MOSI/CS of all three interfaces. USBLC6-4SC6 ESD array on each external port. Start external SPI at 625 kHz. Verify with the actual cables and encoders.
Encoders: onboard MA702GQ on SPI1 (CS = PC6 / ENC1_CS). Port 1 = SPI2 (CS = PC7 / ENC2_CS). Port 2 = SPI3 (CS = PC8 / ENC3_CS).
R39 adds 1 kOhm to the motor NTC. D7 returns cable ESD to GNDA.

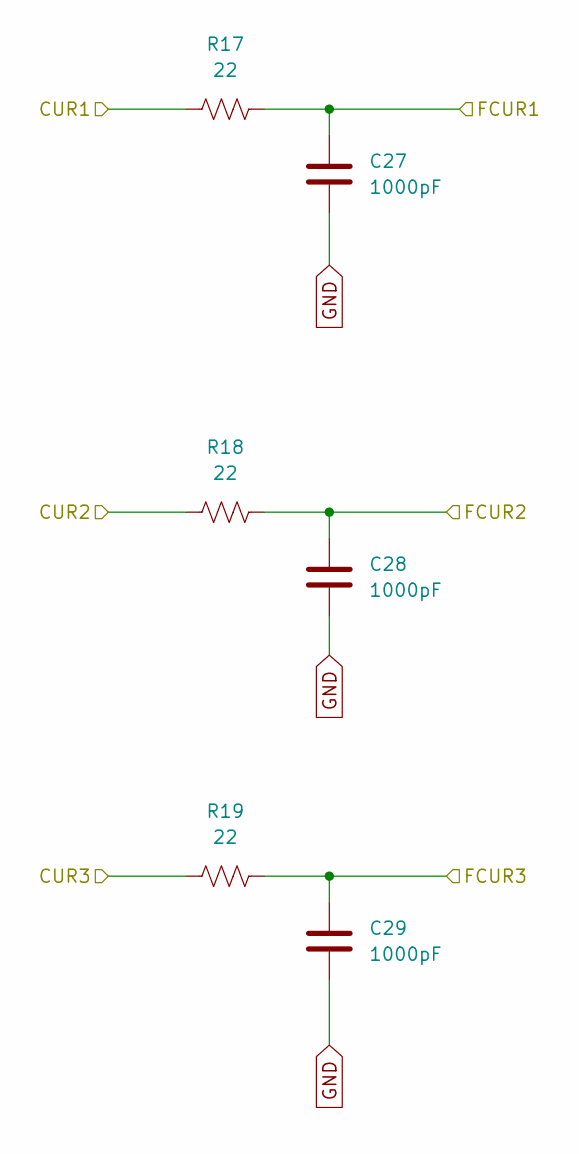
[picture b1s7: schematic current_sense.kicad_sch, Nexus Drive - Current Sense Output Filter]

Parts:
C27, C28, C29: 1000pF; C_0402_1005Metric; MPN MF-CAP-0402-1nF
R17, R18, R19: 22; R_0402_1005Metric; MPN MF-RES-0402-22

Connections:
/CUR1: R17.1; also elsewhere on the board
/CUR2: R18.1; also elsewhere on the board
/CUR3: R19.1; also elsewhere on the board
/CURR_A: C29.1, R19.2; also elsewhere on the board
/CURR_B: C28.1, R18.2; also elsewhere on the board
/CURR_C: C27.1, R17.2; also elsewhere on the board
GND: C27.2, C28.2, C29.2; also elsewhere on the board
